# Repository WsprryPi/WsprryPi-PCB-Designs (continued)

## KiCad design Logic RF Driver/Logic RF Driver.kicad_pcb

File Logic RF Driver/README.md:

# Logic RF Driver

This two-layer board takes a raw 3.3 V CMOS clock and drives it through two paralleled SN74LVC2T45DCUR outputs powered from 5 V. Its target range is 137 kHz–145 MHz. Connect the output to a filter for the selected band, then to a 50-ohm load. The board has no RF power, thermal, emissions, or source-compatibility measurements.

Open [the KiCad project](Logic%20RF%20Driver.kicad_pro) for the schematic and PCB. The project includes the [symbols, footprints, and STEP models](libraries/README.md); their paths use `${KIPRJMOD}`.

## Connections

| Connector | Pin | Connection |
| --- | --- | --- |
| J1, CLOCK IN | Center | Raw 0–3.3 V CMOS clock from a Pico GPIO, Pi GPIO, or Si5351 CLK output |
| J1 | Shield | Ground |
| J2, POWER | 1 | +3.3 V for VCCA and DIR |
| J2 | 2 | +5 V for VCCB |
| J2 | 3 | Common ground |
| J3, RF TO LPF | Center | RF output through C4 to the selected-band filter and load |
| J3 | Shield | Ground |

Connect one clock source at a time, with a common ground for the source, supplies, board, filter, and load. J1 has no 50-ohm termination. The source must supply the desired frequency at valid logic levels; not every Pico, Pi, or Si5351 configuration can generate 145 MHz.

## Circuit

A1 and A2 share the clock input. B1 and B2 connect directly together, with no output resistors. DIR is tied to +3.3 V for A-to-B translation. R1 pulls the input low when it is undriven. C1 bypasses the 3.3 V supply, C2/C3 bypass the 5 V supply, and C4 blocks DC at the output.

The indicator samples `RF_RAW` on the U1 side of C4, through R2 (220 ohms) and C5 (10 nF). D1 is a BAT54S detector, Q1 is an MMBT3904, and D2 is the LED fed from +3.3 V through R4 (680 ohms). R3 is 1 Mohm, and C6 is 10 nF. C6 sits beside D1, with a 1.46 mm cathode connection and a nearby ground via. It stores rectified charge for Q1, while R3 provides a discharge path. The passive and LED footprints are 0603; D1 and Q1 use SOT-23. The detector loads U1's output stage. See the [input-loading study](INPUT-LOADING.md) for the R2 trade-off; its effect on RF output and total supply current is unmeasured and not included in the comparison model.

[TI's datasheet](https://www.ti.com/lit/ds/symlink/sn74lvc2t45.pdf) allows tying two outputs together for stronger drive. The device's electrical and thermal limits apply. Output current sharing and RF power across the target range are unmeasured on this board.

### Why the input is DC-coupled and C4 is on the output

The input needs a ground-referenced LOW and HIGH, so J1 is DC-coupled to A1/A2. R1 keeps it low if the clock source is disconnected or has high impedance. Putting a capacitor ahead of this pull-down removes the DC reference and can produce negative excursions or an unreliable HIGH. An AC-coupled clock or sine-wave source needs a separate bias and conditioning circuit.

The output capacitor has a different job: C4 removes the waveform's average voltage at the filter input. A 0–5 V waveform at 50% duty cycle has a nominal 2.5 V average, provided the downstream circuit gives it a DC return. The signal conductor is DC-blocked; the grounds are connected. See the [C4 impedance and bias analysis](C4-SELECTION.md).

## Parts and assembly

| References | Selected part | Specification | JLCPCB class |
| --- | --- | --- | --- |
| U1 | SN74LVC2T45DCUR / C15741 | VSSOP-8; dual-supply translator | Extended |
| R1 | 0603WAF1002T5E / C25804 | 10 kohms; 1%; 0.1 W; 0603 | Basic |
| R2 | 0603WAF2200T5E / C22962 | 220 ohms; 1%; 0.1 W; 0603 | Basic |
| R3 | 0603WAF1004T5E / C22935 | 1 Mohm; 1%; 0.1 W; 0603 | Basic |
| R4/R5 | 0603WAF6800T5E / C23228 | 680 ohms; 1%; 0.1 W; 0603 | Basic |
| C1/C2 | CC0603KRX7R9BB104 / C14663 | 100 nF; 10%; 50 V; X7R; 0603 | Basic |
| C3/C4 | CL10A105KB8NNNC / C15849 | 1 uF; 10%; 50 V; X5R; 0603 | Basic |
| C5/C6 | 0603B103K500NT / C57112 | 10 nF; 10%; 50 V; X7R; 0603 | Basic |
| D1 | BAT54S,215 / C47546 | 30 V; 200 mA; dual series Schottky; SOT-23 | Extended |
| D2/D3 | KT-0603R / C2286 | Red LED; 0603 | Basic |
| Q1 | MMBT3904(RANGE:100-300) / C20526 | NPN; 40 V; 200 mA; SOT-23 | Basic |

The sixteen-component [BOM](BOM.csv) covers U1, Q1, R1-R5, C1-C6, and D1-D3. Every assembly position has a selected ordering code in the hidden `LCSC Part #` field. The saved **JLCPCB** BOM preset exports the assembly columns and groups matching parts; see the [BOM export instructions](LCSC-PARTS.md#jlcpcb-bom-export). D2 indicates driver-output activity, and D3 indicates the 3.3 V supply through its own R5. J1/J2/J3 are visible in the schematic, board, and rendering, but excluded from the BOM and not marked DNP. J1/J3 use the Adafruit 1865 edge-launch SMA footprint. J2 has a shared footprint for an Adafruit 2136 three-position screw terminal or a straight 1×3 pin header, with 2.54 mm pitch, 1.2 mm holes, and 2.0 mm pads. The screw terminal is the default assembly option. Its body overhangs the board edge by 1.25 mm. The footprint silkscreen ends inside the board edge, while the fab outline and courtyard show the full housing. C1–C3 lie outside its courtyard. See [ordering codes and supplier information](LCSC-PARTS.md) and the [connector and assembly notes](CONNECTORS.md).

## Layout and checks

The board is 27.08 × 16.00 mm, with 1 mm corner radii and a nominal thickness of 1.57 mm. It has two copper layers, 83 front-layer track segments and 41 ground vias. Both layers have a filled ground zone, and stitching runs along both sides of the short RF paths. The placement grid is 0.25 mm, though several component anchors sit off it. See [layout details](PCB-LAYOUT.md).

The configured CAD checks report zero ERC violations, zero unconnected items, and zero schematic-parity issues. The saved PCB has filled ground zones and reports zero DRC violations, zero unconnected items, and zero schematic-parity issues. A local edge-contact rule covers the J1/J3 SMA lands, and all other copper retains the 0.50 mm edge setback. All connections are routed. Connector fit and RF performance remain unmeasured. All PCB DRC and schematic ERC categories are enabled. [Validation](VALIDATION.md) describes the warning checks.

## Project text variables

The PCB Editor exposes these settings under **File → Board Setup → Text & Graphics → Text Variables**. Schematic Setup also includes these definitions. The project file holds 16 variables for title blocks, headings, supply notes, and board labels; they are not machine-wide environment variables.

Edit the project file externally with the KiCad editors and the project closed. KiCad keeps settings in memory and can overwrite an external edit when it closes. Reopen the project to load the file, and check label fit and DRC for the resulting labels. See the [KiCad text-variable reference](https://docs.kicad.org/10.0/en/pcbnew/pcbnew.html#text_variables).

## Research and limitations

The [30 m transmitter/filter study](30M-TRANSMITTER.md) connects the board’s behavioral circuit model directly to the five-element L-first filter and the original seven-element C-first filter at 10.1401 MHz. The nominal L-first case predicts 65.5 mW into 50 ohms and a third harmonic near −76 dBc. Coil Q and line-length sensitivities and finer-timestep checks are included. The C-first comparison demands substantially higher modeled output current. Neither case establishes physical performance, safe current, or emissions compliance.

The [single-chip THS3491 amplifier study](THS3491-STUDY.md) evaluates a separate gain-of-five PA driven by this board, with input and output low-pass filters, supply current, and thermal estimates. Its nominal half-voltage divider predicts about 231–247 mW at the filtered load; the higher-drive divider predicts about 331–356 mW. It does not establish 500 mW across the full range. The PA is absent from the schematic, PCB, and BOM.

The [dual-chip THS3491 study](THS3491-DUAL-STUDY.md) evaluates TI's parallel RGT load-sharing core with inductor-first filters. It predicts about 335–357 mW at the filtered load with the 0.6 divider, compared with 330–344 mW from the matched single-RGT control. Each chip dissipates about 0.92 W, while total IC heat is about 1.84 W. Higher modeled output at 145 MHz requires a pin swing above TI's recommended linear envelope; the study does not establish 500 mW across the full range.

The [25-to-50-ohm THS3491 matching-filter study](THS3491-MATCHING-STUDY.md) evaluates a single RGT amplifier with an inductor-first matching/output filter. It predicts approximately 500 mW at nominal drive and about 600 mW with adjustment headroom. Filter tolerances and losses limit fixed-drive output, and approximately 2 W of IC heat requires a suitable PA thermal layout. It establishes nominal electrical feasibility, with continuous-duty reliability unqualified.

The [dual-chip THS3491 matching-filter study](THS3491-DUAL-MATCHING-STUDY.md) compares two RGT amplifiers with the same 25-to-50-ohm filters, source, losses, and tolerance cases. The 0.50 divider predicts 536–547 mW, with up to 1.32 W of heat per chip and 2.64 W total. The 0.55 divider gives nominal adjustment headroom at 645–662 mW and keeps the selected ±5% output-filter tolerance cases above 500 mW. Combined poorer-Q, higher-loss, and tolerance cases fall below 500 mW, and actual cooling and RF performance remain unqualified. The PA is absent from this project's CAD and BOM.

The [output-sharing resistor study](OUTPUT-SHARING.md) evaluates independent resistors on B1/B2. TI permits directly paralleling the two outputs, which is the design baseline. For optional resistive isolation, 10 ohms per output gives about 65–68 mW into 50 ohms in the model. Hypothetical skew tests do not demonstrate a need for these resistors. These resistors are absent from the schematic, PCB, and BOM.

The [board circuit simulation](BOARD-SIMULATION.md) includes the RF_RAW detector and both LED branches. Its nominal model predicts about 82.5 mW at 137 kHz and 79.9 mW at 145 MHz into 50 ohms, excluding filter and connector loss. Assumed-skew stress cases explore model sensitivity; their current peaks are not validated predictions of this IC or evidence of a timing fault. The study has no extracted PCB or supply-network model and does not establish thermal or full-band reliability.

The [SN74LVC2T45 versus BS170 comparison](COMPARISON.md) predicts about 84.32 mW at 137 kHz and 83.03 mW at 145 MHz for the paralleled logic stage, excluding filter loss. It uses a behavioral logic model, ideal supplies, and a bias-dependent C4 fit. These figures are simulated, not measured, and exclude the detector branch. The separate [detector study](INPUT-LOADING.md) gives about 82.48 mW at 137 kHz and 79.89 mW at 145 MHz with R2 at 220 ohms, using surrogate semiconductor and LED models. The ideal-choke BS170 results are diagnostic only because they fail numerical robustness checks. See [model scope](MODEL-SCOPE.md).

Project-owned work follows the repository [MIT license](../LICENSE.md). Library assets retain the [KiCad library license and exception](libraries/KICAD-LIBRARY-LICENSE.md). Manufacturer data retain their own terms.

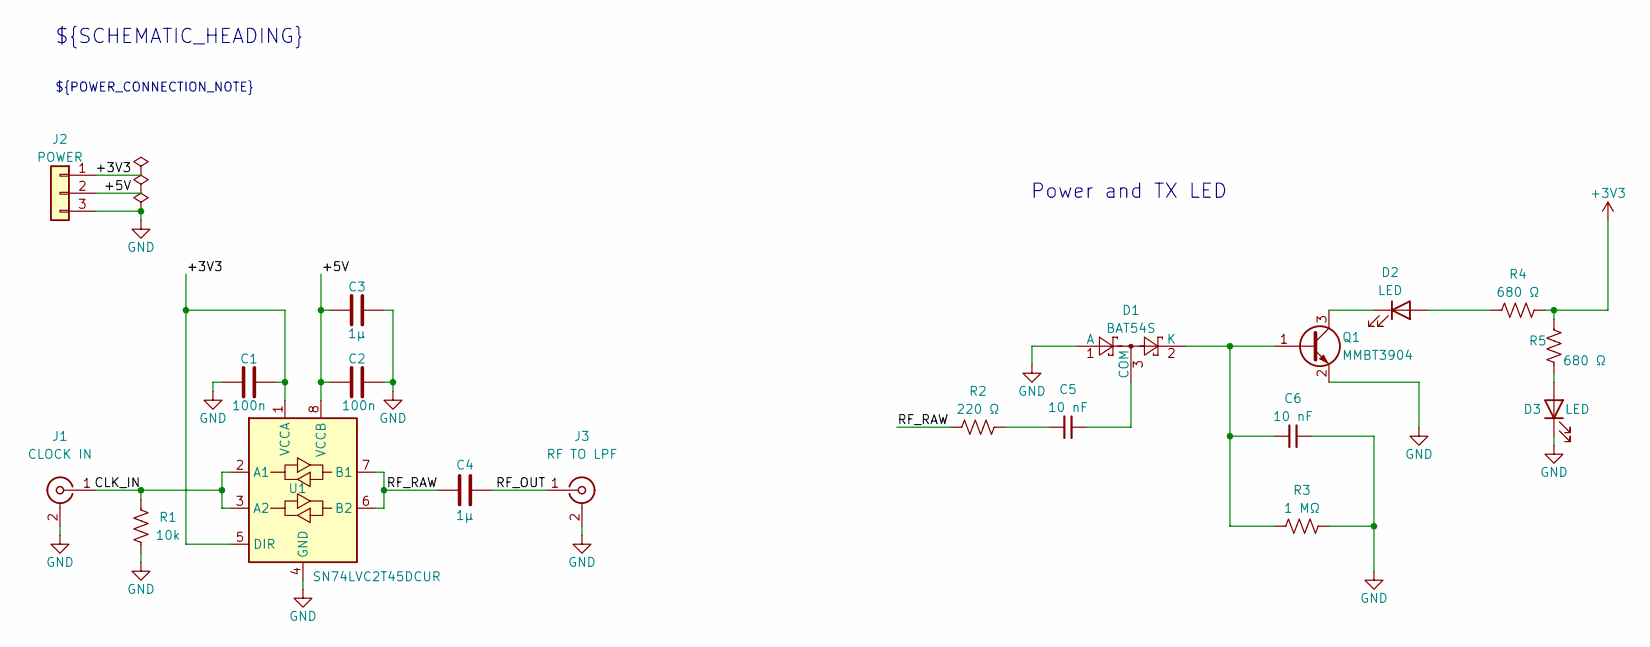
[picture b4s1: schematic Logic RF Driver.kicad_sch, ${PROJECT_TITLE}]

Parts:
C1, C2: 100n; C_0603_1608Metric; Voltage 50 V; Tolerance ±10%; MPN CC0603KRX7R9BB104; LCSC Part # C14663
C3, C4: 1μ; C_0603_1608Metric; Voltage 50 V; Tolerance ±10%; MPN CL10A105KB8NNNC; LCSC Part # C15849
C5, C6: 10 nF; C_0603_1608Metric; Voltage 50 V; Tolerance 10%; MPN 0603B103K500NT; JLCPCB Class Basic
D1: BAT54S; SOT-23; MPN BAT54S,215; JLCPCB Class Extended
D2, D3: LED; LED_KT0603R; MPN KT-0603R; JLCPCB Class Basic
J1: CLOCK IN; SMA_Adafruit_1865_EdgeLaunch; MPN 1865
J2: POWER; Power_1x03_P2.54mm_Header_or_Adafruit_2136; MPN 2136
J3: RF TO LPF; SMA_Adafruit_1865_EdgeLaunch; MPN 1865
Q1: MMBT3904; SOT-23; MPN MMBT3904(RANGE:100-300); JLCPCB Class Basic
R1: 10k; R_0603_1608Metric; Tolerance 1%; Rating 0.1 W; MPN 0603WAF1002T5E; LCSC Part # C25804
R2: 220 Ω; R_0603_1608Metric; Voltage 75 V; Rating 0.1 W; MPN 0603WAF2200T5E; JLCPCB Class Basic
R3: 1 MΩ; R_0603_1608Metric; Voltage 75 V; Rating 0.1 W; MPN 0603WAF1004T5E; JLCPCB Class Basic
R4, R5: 680 Ω; R_0603_1608Metric; Voltage 75 V; Rating 0.1 W; MPN 0603WAF6800T5E; JLCPCB Class Basic
U1: SN74LVC2T45DCUR; VSSOP-8_2.3x2mm_P0.5mm; MPN SN74LVC2T45DCUR; LCSC Part # C15741

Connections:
+3V3: C1.1, J2.1, R4.2, R5.2, U1.1 (VCCA), U1.5 (DIR)
/+5V: C2.1, C3.1, J2.2, U1.8 (VCCB)
/CLK_IN: J1.1 (In), R1.1, U1.2 (A1), U1.3 (A2)
/RF_OUT: C4.2, J3.1 (In)
/RF_RAW: C4.1, R2.1, U1.6 (B2), U1.7 (B1)
GND: C1.2, C2.2, C3.2, C6.2, D1.1 (A), D3.2 (K_1), J1.2 (Ext), J2.3, J3.2 (Ext), Q1.2 (E), R1.2, R3.2, U1.4 (GND)
unnamed: C5.1, R2.2
unnamed: C5.2, D1.3 (COM)
unnamed: C6.1, D1.2 (K), Q1.1 (B), R3.1
unnamed: D2.1 (A_2), R4.1
unnamed: D2.2 (K_1), Q1.3 (C)
unnamed: D3.1 (A_2), R5.1

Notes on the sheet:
${SCHEMATIC_HEADING}
Power and TX LED
${POWER_CONNECTION_NOTE}

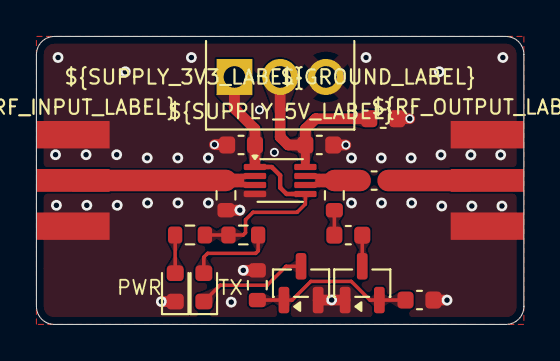
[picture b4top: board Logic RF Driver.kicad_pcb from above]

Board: 2 copper layers, 27.1 x 16.0 mm, 19 parts (0 on the bottom side), 12 nets.

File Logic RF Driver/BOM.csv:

"Comment","Designator","Footprint","LCSC Part #","Quantity","Manufacturer","MPN"
"100n","C1,C2","SN74LVC2T45_Amp:C_0603_1608Metric","C14663","2","YAGEO","CC0603KRX7R9BB104"
"1μ","C3,C4","SN74LVC2T45_Amp:C_0603_1608Metric","C15849","2","Samsung Electro-Mechanics","CL10A105KB8NNNC"
"10 nF","C5,C6","SN74LVC2T45_Amp:C_0603_1608Metric","C57112","2","FH (Guangdong Fenghua Advanced Tech)","0603B103K500NT"
"BAT54S","D1","SN74LVC2T45_Amp:SOT-23","C47546","1","Nexperia","BAT54S,215"
"LED","D2,D3","SN74LVC2T45_Amp:LED_KT0603R","C2286","2","Hubei KENTO Elec","KT-0603R"
"MMBT3904","Q1","SN74LVC2T45_Amp:SOT-23","C20526","1","Jiangsu Changjing Electronics Technology Co., Ltd.","MMBT3904(RANGE:100-300)"
"10k","R1","SN74LVC2T45_Amp:R_0603_1608Metric","C25804","1","UNI-ROYAL(Uniroyal Elec)","0603WAF1002T5E"
"220 Ω","R2","SN74LVC2T45_Amp:R_0603_1608Metric","C22962","1","UNI-ROYAL(Uniroyal Elec)","0603WAF2200T5E"
"1 MΩ","R3","SN74LVC2T45_Amp:R_0603_1608Metric","C22935","1","UNI-ROYAL(Uniroyal Elec)","0603WAF1004T5E"
"680 Ω","R4,R5","SN74LVC2T45_Amp:R_0603_1608Metric","C23228","2","UNI-ROYAL(Uniroyal Elec)","0603WAF6800T5E"
"SN74LVC2T45DCUR","U1","SN74LVC2T45_Amp:VSSOP-8_2.3x2mm_P0.5mm","C15741","1","Texas Instruments","SN74LVC2T45DCUR"

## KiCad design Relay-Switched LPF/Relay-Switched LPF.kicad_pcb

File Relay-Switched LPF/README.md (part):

# Relay-Switched LPF

Independent KiCad reconstruction of the **QRP Labs Ultimate relay-switched LPF carrier, PCB Rev. 5**. Open [Relay-Switched LPF.kicad_pro](Relay-Switched%20LPF.kicad_pro). The editable [schematic](Relay-Switched%20LPF.kicad_sch), [PCB](Relay-Switched%20LPF.kicad_pcb), and [schematic PDF](Relay-Switched%20LPF.pdf) belong to this project.

**Engineering reconstruction, drawing revision v0.0.1; not qualified for fabrication or use.** The published circuit is reconstructed, and a new two-layer layout is provided inside an 80 × 37 mm outline. This is not an original QRP Labs CAD release, an exact trace copy, or a verified mechanical replacement. Read [VALIDATION.md](VALIDATION.md) for actual checks and remaining findings before ordering anything.

## What is included

- Five Panasonic TX2-5V DPDT relay channels, five 1N4148 flyback diodes, and ten four-position LPF sockets.
- An underside 2 × 5 host socket, active-low band controls, separate coil-supply link, five output selectors, a final-filter input selector, and an optional output-ground bypass.
- Five individual antenna solder-terminal pairs, a final-output terminal pair, and alternative generic vertical and edge SMA pad groups.
- Independent [symbol library](relay-switched-lpf.kicad_sym), [footprint library](relay-switched-lpf.pretty/), and `${KIPRJMOD}` library tables. No references to other repository projects or machine-specific library locations.
- [Project-local 3D models](relay-switched-lpf.3dshapes/README.md) for the carrier components, optional SMA connectors, and default fitted wire links; the four mounting-hole footprints are also local.
- [Reconstruction generator](design/generate.py), [routing script](design/route.py), and [connectivity audit](design/audit.py). These are reproducibility tools; the saved native CAD files remain authoritative after hand edits.
- Ten four-pin LPF connectors use the standard KiCad boxed `Conn_01x04` appearance, adapted in the project-local `LPF_IN`/`LPF_OUT` symbols; see [attribution and license](KICAD-LIBRARY-LICENSE.md#four-pin-connector-symbols).
- J21–J26 use the matching two-pin boxed connector appearance, adapted locally from KiCad `Conn_01x02`; see [attribution](KICAD-LIBRARY-LICENSE.md#two-pin-antenna-connector-symbol).
- W1–W9 use matching boxed two-/three-pin connector symbols. These are drawing conventions; the PCB retains bare wire-link pads and the assembly options below.
- J1 uses the same boxed connector style for its ten schematic pins; its physical footprint remains the underside 2 × 5 host socket.
- X1/X2 use project-local copies of the KiCad `Conn_Coaxial` symbol, with center contact 1 on `LPF1_OUT` and shield 2 on `GND_OUT`; their vertical/edge SMA footprints remain distinct.
- Ground markings use the project-local `GND` power symbol matching W8’s triangular ground. Main ground is global `GND`; `GND_OUT` remains separate. A local `PWR_FLAG` records the host-supplied ground for ERC.
- A visibly wired schematic arranged like the published diagram: relay coils and flyback diodes above the shared RF input bus, five filter columns, and a shared output bus below. Relay units A/B/C are the coil/input pole/output pole of the same physical relay. [Redraw tool](design/redraw_schematic.py) updates the schematic and its local symbol graphics without writing the PCB.

The plug-in filter circuits, band-dependent inductors/capacitors, Ultimate3S transmitter, sixth relay/filter on that transmitter, GPIO drivers, enclosure, and spacers are external. No arbitrary filter bands or component values have been selected.

## Default circuit and assembly

Install the highest-frequency LPF in **slot 1**, on the right. Energizing one of relays 2–5 selects its filter, whose output feeds slot 1 through the common `RFO` bus. Energizing relay 1 feeds its filter directly from `RFI`. With no carrier relay energized, an external filter-0 signal on `RFO` can still pass through slot 1. Filters 2–5 have both RF terminals grounded when their relays are at rest.

The saved PCB represents **unbridged wire-link pads**. Fit these six separate wire links for the default LPF configuration:

| Link | Fit | Function |
| --- | --- | --- |
| W1 | 1–2 | Connect `+5V` to `RELAY_VPLUS` |
| W2 | **Open** | Slot-1 relay output selector; final output already comes directly from LPF1 |
| W3, W4, W5, W6 | Each 1–2 | Connect relays 2–5 to `RFO` |
| W7 | 1–2 | Feed relay-1 normally closed input from `RFO` |
| W8 | **Open** | Preserve isolated final output return |
| W9 | **Open** | Optional LPF1-output to relay-1 second-pole COM link |

W2–W6 each use pin 1 for the relay's output NO contact, pin 2 for `RFO`, and pin 3 for the corresponding individual `ANTn` terminal. W7 pins 1/2/3 are `RFO` / `FINAL_NC` / `GND`. W8 pins 1/2 are `GND` / `GND_OUT`. W9 pins 1/2 are `LPF1_OUT` / `FINAL_RELAY_COM`; it represents the separately accessible RF pads by relay 1 in the source circuit. The second pole of relay 1 is not in the default RF path. Link designators and pad ordering are assigned by this reconstruction, not original QRP Labs designators. An unfitted selector pad still has a routed net; it is intentionally not shorted by copper.

`GND_OUT` joins X1/X2 returns, J26 pin 2, and slot-1 output-socket pins 3/4. It remains separate from main `GND`; slot-1 output-socket pins 1/2 carry RF. Do not bridge these returns through mounting hardware, coax shields, or test equipment without considering the intended filter return path. W8 represents the original optional ground-bridge pad pairs as one two-terminal link, not a default connection.

The circuit retains alternate output selection pads, but this revision has only been audited against the default LPF configuration. Alternate BPF or separate-antenna assembly requires a separate connection review. The SMA groups are permanently connected to `LPF1_OUT`, not `RFO`; those nets are distinct.

For a **separate regulated 5 V relay supply**, leave W1 **open**, connect supply positive to **W1 pin 2 (`RELAY_VPLUS`)**, and connect supply negative to main **`GND`**, shared with the host/low-side drivers. Do not use `GND_OUT` as the coil return. W1 pin 1 remains on host `+5V`; keep W1 open so the two positive supplies are not paralleled. The relays remain 5 V types. Use external sink drivers compatible with the coil supply and host power sequencing. The default shared-supply configuration still fits W1 pins 1–2.

This cathode-to-coil-supply connection is an intentional adaptation of the reconstructed QRP Labs circuit. CAD connectivity and rule checks pass; separate-supply switching behavior has not been bench-qualified.

## Host and module pin maps

J1 is on **B.Cu**, opposite the relays. In a component-side/top view, with slot 5 on the left and slot 1 on the right, J1's odd-numbered column is on the left, and its even-numbered column is on the right. Read each row from the input-socket edge toward the output-socket edge:

| Left pin | Net | Right pin | Net |
| --- | --- | --- | --- |
| 1 | +5V | 2 | BAND5_N |
| 3 | BAND3_N | 4 | BAND4_N |
| 5 | BAND1_N | 6 | BAND2_N |
| 7 | GND | 8 | RFI |
| 9 | GND | 10 | RFO |

This numeric convention is assigned to the published labeled pad arrangement. Confirm the mating host's numbering and orientation; do not infer compatibility from a generic 2 × 5 socket name. In top view, J1 pin 1 is at board coordinate (2.54, 8.26) mm, with 2.54 mm row/column pitch.

Band controls sink the relay-coil current. The nominal 5 V, 140 mW coil corresponds to approximately 28 mA. Use a suitable external sink driver for Raspberry Pi/Pico GPIO; the carrier contains no transistor or level shifter. Energize **at most one** band input at a time and mute RF during switching. D1–D5 cathodes connect directly to `RELAY_VPLUS`, the same rail as the relay coil positives, so flyback current stays on the coil-supply rail.

| Item | Pin assignments |
| --- | --- |
| RLn | 1 coil+, 12 coil−; 8 NO/input bus, 9 COM/filter input, 10 NC; 5 NO/output selector, 4 COM/filter output for slots 2–5 (separate FINAL_RELAY_COM for slot 1), 3 NC/main ground |
| Dn | 1 cathode/+5V; 2 anode/BANDn_N |
| J2/J4/J6/J8/J10 | LPF1/2/3/4/5 input: pins 1/2 GND; pins 3/4 signal |
| J3/J5/J7/J9/J11 | LPF1/2/3/4/5 output: pins 1/2 signal; pins 3/4 GND except LPF1 pins 3/4 use GND_OUT |
| J21–J25 | ANT1–ANT5: pin 1 RF, pin 2 main GND |
| J26, X1, X2 | Pin 1 final RF output, pin 2 isolated GND_OUT; repeated X1/X2 pin 2 pads are intentional |

Input sockets run pin 1 left to pin 4 right in top view. Output sockets run pin 4 left to pin 1 right. Match module IN/OUT markings. There is no guaranteed RF power, frequency range, insertion loss, or isolation rating for the reconstructed layout.

## Geometry, population, and model limits

| Feature | Implemented geometry | Evidence / limit |
| --- | --- | --- |
| Outline | 80 × 37 mm, two layers, four tangent R3 mm corner fillets | Overall published size retained; radius selected for this reconstruction, not a measured original-board radius |
| Filter sockets | 2.54 mm pitch; 33.02 mm input/output row spacing; 13.97 mm slot spacing | Pitch-based reconstruction of the placement/trace drawings; confirm on real modules |
| Mounts | Four 3.2 mm NPTH holes at (3,3), (77,3), (3,34), (77,34) mm | **Inferred**, not dimensioned in the manual; must be measured against host/spacers |
| Relays | 15 × 7.4 mm body; 5.08 mm pin-row separation, 5.08/2.54/2.54 mm longitudinal pin spacing; 1 mm drills | Standard TX2 terminal pattern reconstructed from available pin/dimension evidence; verify actual supplied surplus relay |
| Diodes | DO-35 axial, 7.62 mm lead pitch | New footprint choice, not a measured original lead bend |
| Wire links / terminals | Bare 1.8 mm pads, 1 mm holes, 2.54 mm pitch | Layout adaptation; not plastic headers |
| X1 | Generic vertical SMA, central signal and four returns at ±2.54 mm; center (75.819, 23) mm | CAD edge and courtyard checks pass; no selected manufacturer/order code or verified physical fit |
| X2 | Generic double-sided edge SMA land pattern; footprint origin (78.5, 12) mm, with RF and isolated-return layer transitions | CAD clearance/connectivity checks pass; no selected connector or qualified board thickness |
| Routing | New 0.30 mm two-layer traces with ground and isolated-return fills | Not an exact original trace geometry or controlled-impedance stackup |

The terminal and link locations have been adjusted within the published outline to make the reconstruction routable. Consequently, mating compatibility is not established by matching the board's outer dimensions. X1 is an alternative to X2/J26; using a short coax pigtail on the output pads avoids assuming a generic SMA fits underneath a filter. Review vertical clearances to the plug-in filters and the original warning about vertical SMA interference.

The output-area DRC repair moves RL1 left 0.762 mm and X1 left 0.381 mm from their initial placements, preserving socket/mounting coordinates. Nearby RFI, LPF1 input, and relay-1 COM traces are rerouted. Two 0.65/0.30 mm vias join X2's RF lands and its isolated output return between copper layers. The latest hand edit extends both main-ground pours across the board, with clearance around the separate output-return pads and traces. Two dedicated return vias and short traces now connect X2’s front/back ground lands. KiCad 10.0.6 reports zero rule violations, unconnected items, or schematic-parity findings; see [current validation](VALIDATION.md#output-return-layer-repair--2026-11-13). Physical connector fit and RF qualification remain open.

The 3D viewer now uses seven local STEP/VRML assets across 29 model instances: the 21 normal carrier components, both optional SMA alternatives, and six fitted wire links. The socket and diode STEP files are unmodified KiCad assets; the relay, SMA, and wire models are documented original nominal previews. No unrelated relay/connector model is silently substituted. Bare terminals, open links, and mounting holes have no invented part bodies. See [model coverage and limits](relay-switched-lpf.3dshapes/README.md) and [KiCad asset terms](KICAD-LIBRARY-LICENSE.md).

Twenty-one normal carrier components are needed before wire links: five relays, five diodes, ten four-way sockets, and one ten-way underside socket. SMA hardware is optional; filter modules, six default wire links, and mounting hardware are separate assembly items. The two SMA previews are alternatives, not an instruction to assemble both. See [BOM.csv](BOM.csv).

All 42 saved board footprints, including the four mounting holes, resolve to eleven project-local footprint definitions. The six fitted wire links use model-bearing variants whose pad geometry is identical to the bare versions. Every schematic symbol is in the independent local symbol library. Keep the entire project folder, including `.pretty` and `.3dshapes`, together when copying it.

## Letter sheets and shared title-block fields

The schematic fits on one **US Letter landscape sheet, 11 × 8.5 inches**, matching the selected ANSI A page setting in both editors. The compact symbols use a standard 25 mil schematic connection grid. The PCB drawing-sheet size is the same; its actual board geometry is unchanged by this page-format work.

Edit shared values under **Schematic Setup or Board Setup → Project → Text Variables**. Both title blocks refer to the same project variables, so set these values once rather than replacing their `${DOC_...}` references in Page Settings:

| Project variable | Shared field | Current value |
| --- | --- | --- |
| `DOC_TITLE` | Title | Relay-Switched LPF |
| `DOC_DATE` | Date | 11/13/2026 |
| `DOC_REVISION` | Revision | v0.0.1 |
| `DOC_COMPANY` | Company / author | Lee Bussy [AA0NT] |
| `DOC_COMMENT1`–`DOC_COMMENT4` | Comments 1–4 | Empty |
| `DOC_COMMENT5`–`DOC_COMMENT9` | Additional optional comment placeholders | Define shared variables if used |

These are native [KiCad project text variables](https://docs.kicad.org/10.0/en/eeschema/eeschema.html), stored in the `.kicad_pro` file and usable by both editors. The date is an explicit shared value, not an automatic clock. [Shared-field setup tool](design/shared_fields.py) installs the references while retaining existing project values; the redraw and full-generation tools preserve those values on later runs. The filenames and sheet numbers remain editor-specific.

## Rebuilding and checking

Creation and checks use **KiCad 10.0.6**. The generators overwrite this project's CAD; save hand edits before regenerating. Run `design/generate.py` and then `design/route.py` using a Python installation with KiCad's `pcbnew`, wxPython, and NumPy. On macOS, the bundled KiCad Python requires access to the logged-in display session. Routing refuses an already routed board.

The full generator invokes `design/redraw_schematic.py` after creating the initial circuit. To rebuild only the schematic presentation from the saved references and connection map, run `python3 design/redraw_schematic.py`; this uses only Python's standard library. Re-export the PDF and rerun ERC and the connectivity audit afterward. Net labels are retained for names, host connections, and ground references; the filter and relay interconnections are drawn as wires.

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
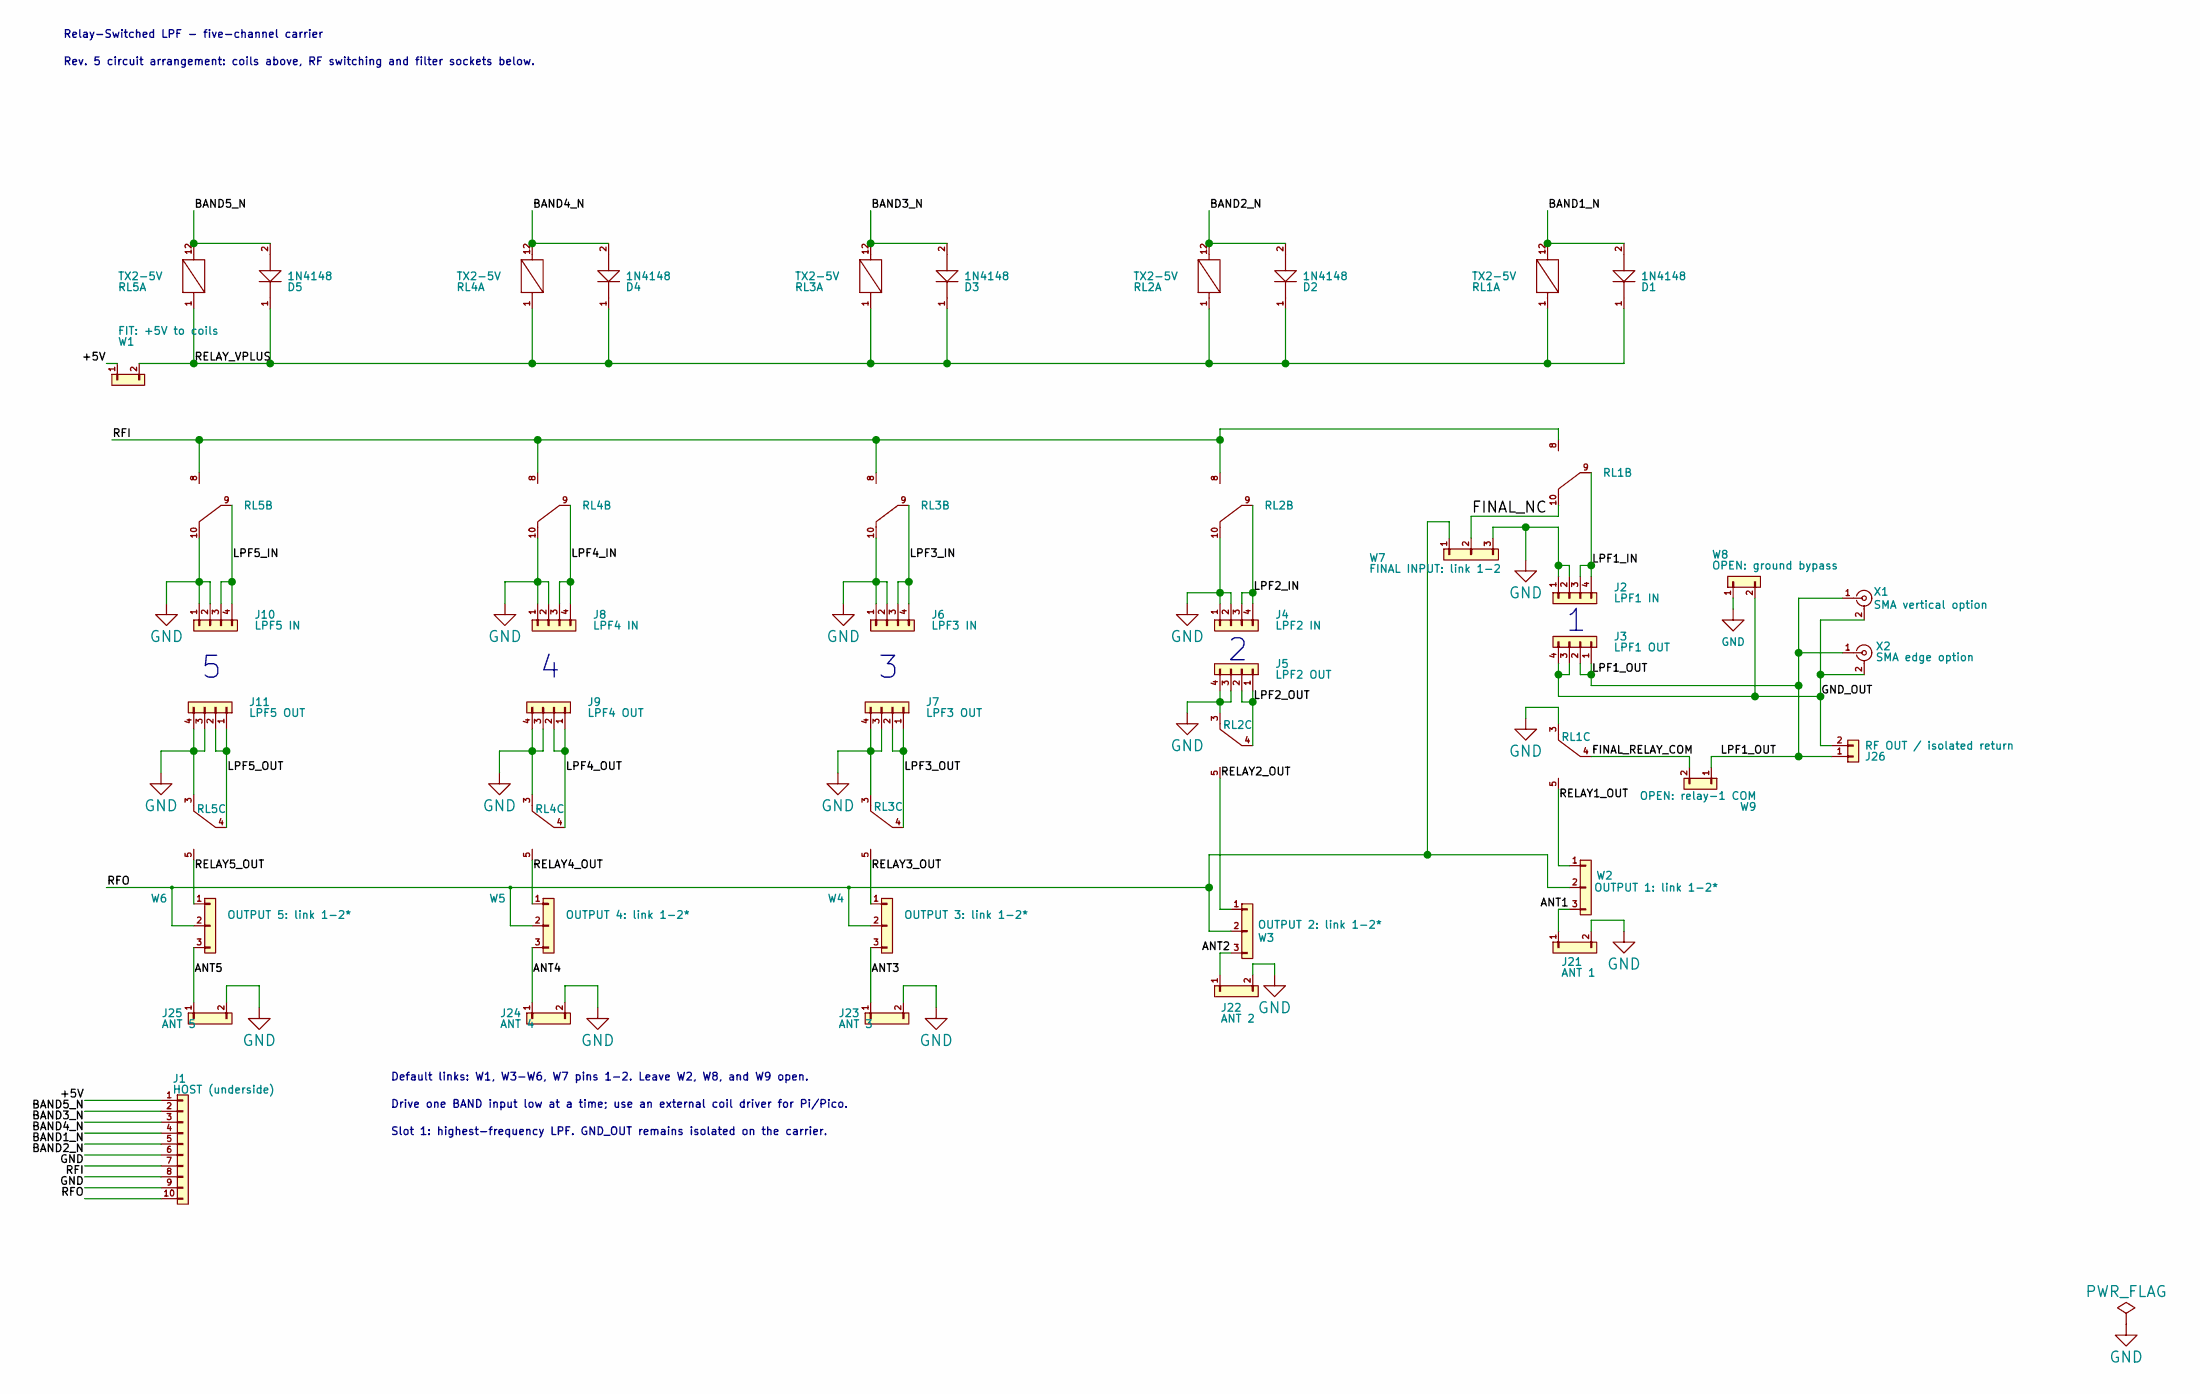
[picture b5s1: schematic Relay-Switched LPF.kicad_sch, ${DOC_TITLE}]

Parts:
D1, D2, D3, D4, D5: 1N4148; D_DO35_P7.62
J1: HOST (underside); Host_2x05
J2: LPF1 IN; Socket_1x4
J3: LPF1 OUT; Socket_1x4
J4: LPF2 IN; Socket_1x4
J5: LPF2 OUT; Socket_1x4
J6: LPF3 IN; Socket_1x4
J7: LPF3 OUT; Socket_1x4
J8: LPF4 IN; Socket_1x4
J9: LPF4 OUT; Socket_1x4
J10: LPF5 IN; Socket_1x4
J11: LPF5 OUT; Socket_1x4
J21: ANT 1; Wire_1x2
J22: ANT 2; Wire_1x2
J23: ANT 3; Wire_1x2
J24: ANT 4; Wire_1x2
J25: ANT 5; Wire_1x2
J26: RF OUT / isolated return; Wire_1x2
RL1, RL2, RL3, RL4, RL5: TX2-5V; TX2_5V
W1: FIT: +5V to coils; Wire_1x2_Link12
W2: OUTPUT 1: link 1-2*; Wire_1x3
W3: OUTPUT 2: link 1-2*; Wire_1x3_Link12
W4: OUTPUT 3: link 1-2*; Wire_1x3_Link12
W5: OUTPUT 4: link 1-2*; Wire_1x3_Link12
W6: OUTPUT 5: link 1-2*; Wire_1x3_Link12
W7: FINAL INPUT: link 1-2; Wire_1x3_Link12
W8: OPEN: ground bypass; Wire_1x2
W9: OPEN: relay-1 COM; Wire_1x2
X1: SMA vertical option; SMA_Vertical_Generic
X2: SMA edge option; SMA_Edge_Generic

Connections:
/+5V: J1.1, W1.1
/ANT1: J21.1, W2.3
/ANT2: J22.1, W3.3
/ANT3: J23.1, W4.3
/ANT4: J24.1, W5.3
/ANT5: J25.1, W6.3
/BAND1_N: D1.2, J1.5, RL1.12
/BAND2_N: D2.2, J1.6, RL2.12
/BAND3_N: D3.2, J1.3, RL3.12
/BAND4_N: D4.2, J1.4, RL4.12
/BAND5_N: D5.2, J1.2, RL5.12
/FINAL_NC: RL1.10, W7.2
/FINAL_RELAY_COM: RL1.4, W9.2
/GND_OUT: J3.3, J3.4, J26.2, W8.2, X1.2 (Ext), X2.2 (Ext)
/LPF1_IN: J2.3, J2.4, RL1.9
/LPF1_OUT: J3.1, J3.2, J26.1, W9.1, X1.1 (In), X2.1 (In)
/LPF2_IN: J4.3, J4.4, RL2.9
/LPF2_OUT: J5.1, J5.2, RL2.4
/LPF3_IN: J6.3, J6.4, RL3.9
/LPF3_OUT: J7.1, J7.2, RL3.4
/LPF4_IN: J8.3, J8.4, RL4.9
/LPF4_OUT: J9.1, J9.2, RL4.4
/LPF5_IN: J10.3, J10.4, RL5.9
/LPF5_OUT: J11.1, J11.2, RL5.4
/RELAY1_OUT: RL1.5, W2.1
/RELAY2_OUT: RL2.5, W3.1
/RELAY3_OUT: RL3.5, W4.1
/RELAY4_OUT: RL4.5, W5.1
/RELAY5_OUT: RL5.5, W6.1
/RELAY_VPLUS: D1.1, D2.1, D3.1, D4.1, D5.1, RL1.1, RL2.1, RL3.1, RL4.1, RL5.1, W1.2
/RFI: J1.8, RL1.8, RL2.8, RL3.8, RL4.8, RL5.8
/RFO: J1.10, W2.2, W3.2, W4.2, W5.2, W6.2, W7.1
GND: J1.7, J1.9, J2.1, J2.2, J4.1, J4.2, J5.3, J5.4, J6.1, J6.2, J7.3, J7.4, J8.1, J8.2, J9.3, J9.4, J10.1, J10.2, J11.3, J11.4, J21.2, J22.2, J23.2, J24.2, J25.2, RL1.3, RL2.3, RL2.10, RL3.3, RL3.10, RL4.3, RL4.10, RL5.3, RL5.10, W7.3, W8.1

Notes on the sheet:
Slot 1: highest-frequency LPF. GND_OUT remains isolated on the carrier.
Relay-Switched LPF - five-channel carrier
Drive one BAND input low at a time; use an external coil driver for Pi/Pico.
Default links: W1, W3-W6, W7 pins 1-2. Leave W2, W8, and W9 open.
Rev. 5 circuit arrangement: coils above, RF switching and filter sockets below.

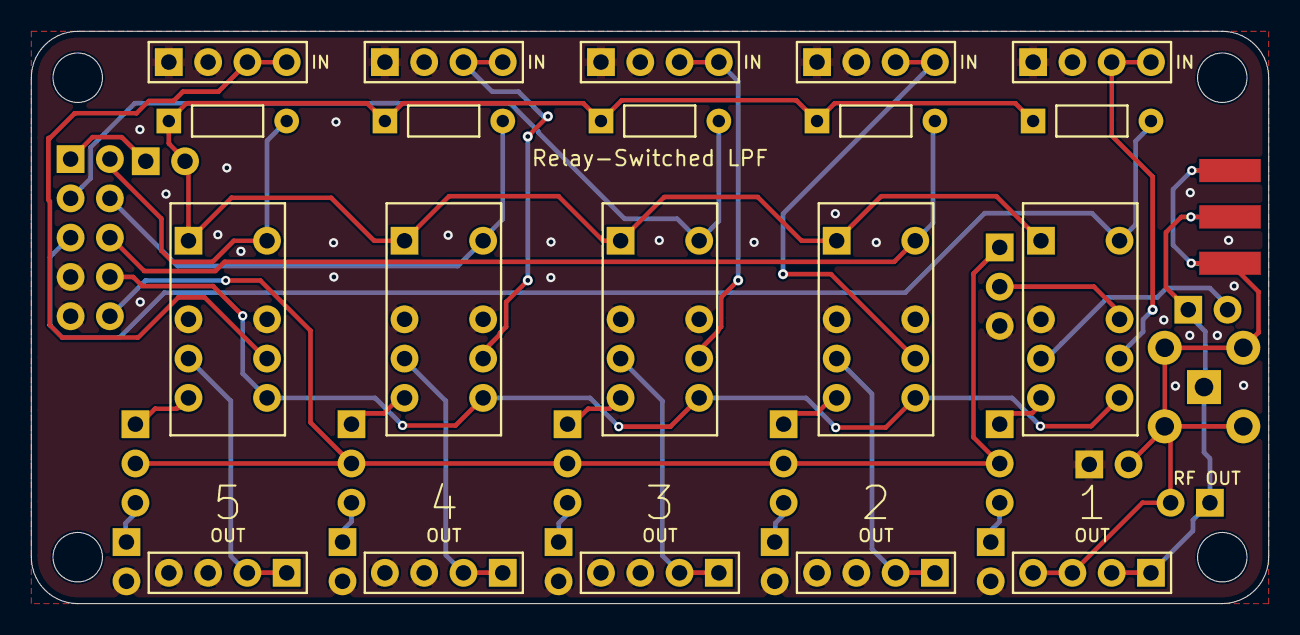
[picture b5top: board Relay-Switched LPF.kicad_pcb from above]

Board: 2 copper layers, 80.0 x 37.0 mm, 42 parts (1 on the bottom side), 33 nets.

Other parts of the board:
H1, H2, H3, H4: Mount 3.2 mm (inferred); MountingHole_3.2mm

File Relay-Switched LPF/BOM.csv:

References,Quantity,Description,Part or specification,Population
RL1-RL5,5,DPDT non-latching relay,Panasonic TX2-5V 5V coil,Required
D1-D5,5,Axial flyback diode,1N4148 DO-35,Required
J2-J11,10,LPF module female socket,1x04 2.54mm pitch through-hole,Required
J1,1,Underside host female socket,2x05 2.54mm pitch through-hole verify mating height,Required
W1 W3 W4 W5 W6 W7,6,Hand-fit wire link,Connect pins 1-2 per README,Default LPF configuration
W2 W8 W9,0,Unfitted optional link,Leave open in default assembly,Open
J21-J26,0,Bare RF wire terminals,PCB pads no purchased header required,Use as needed
X1,0,Optional vertical SMA,Generic pattern no selected order code,Optional fit unverified
X2,0,Optional edge SMA,Generic pattern no selected order code,Optional fit unverified
H1-H4,4,Mounting hardware,Builder choice measure hole positions and stack height,Mechanical fit unverified
External LPFs,5,Plug-in filter modules,Select band set separately highest frequency in slot 1,External

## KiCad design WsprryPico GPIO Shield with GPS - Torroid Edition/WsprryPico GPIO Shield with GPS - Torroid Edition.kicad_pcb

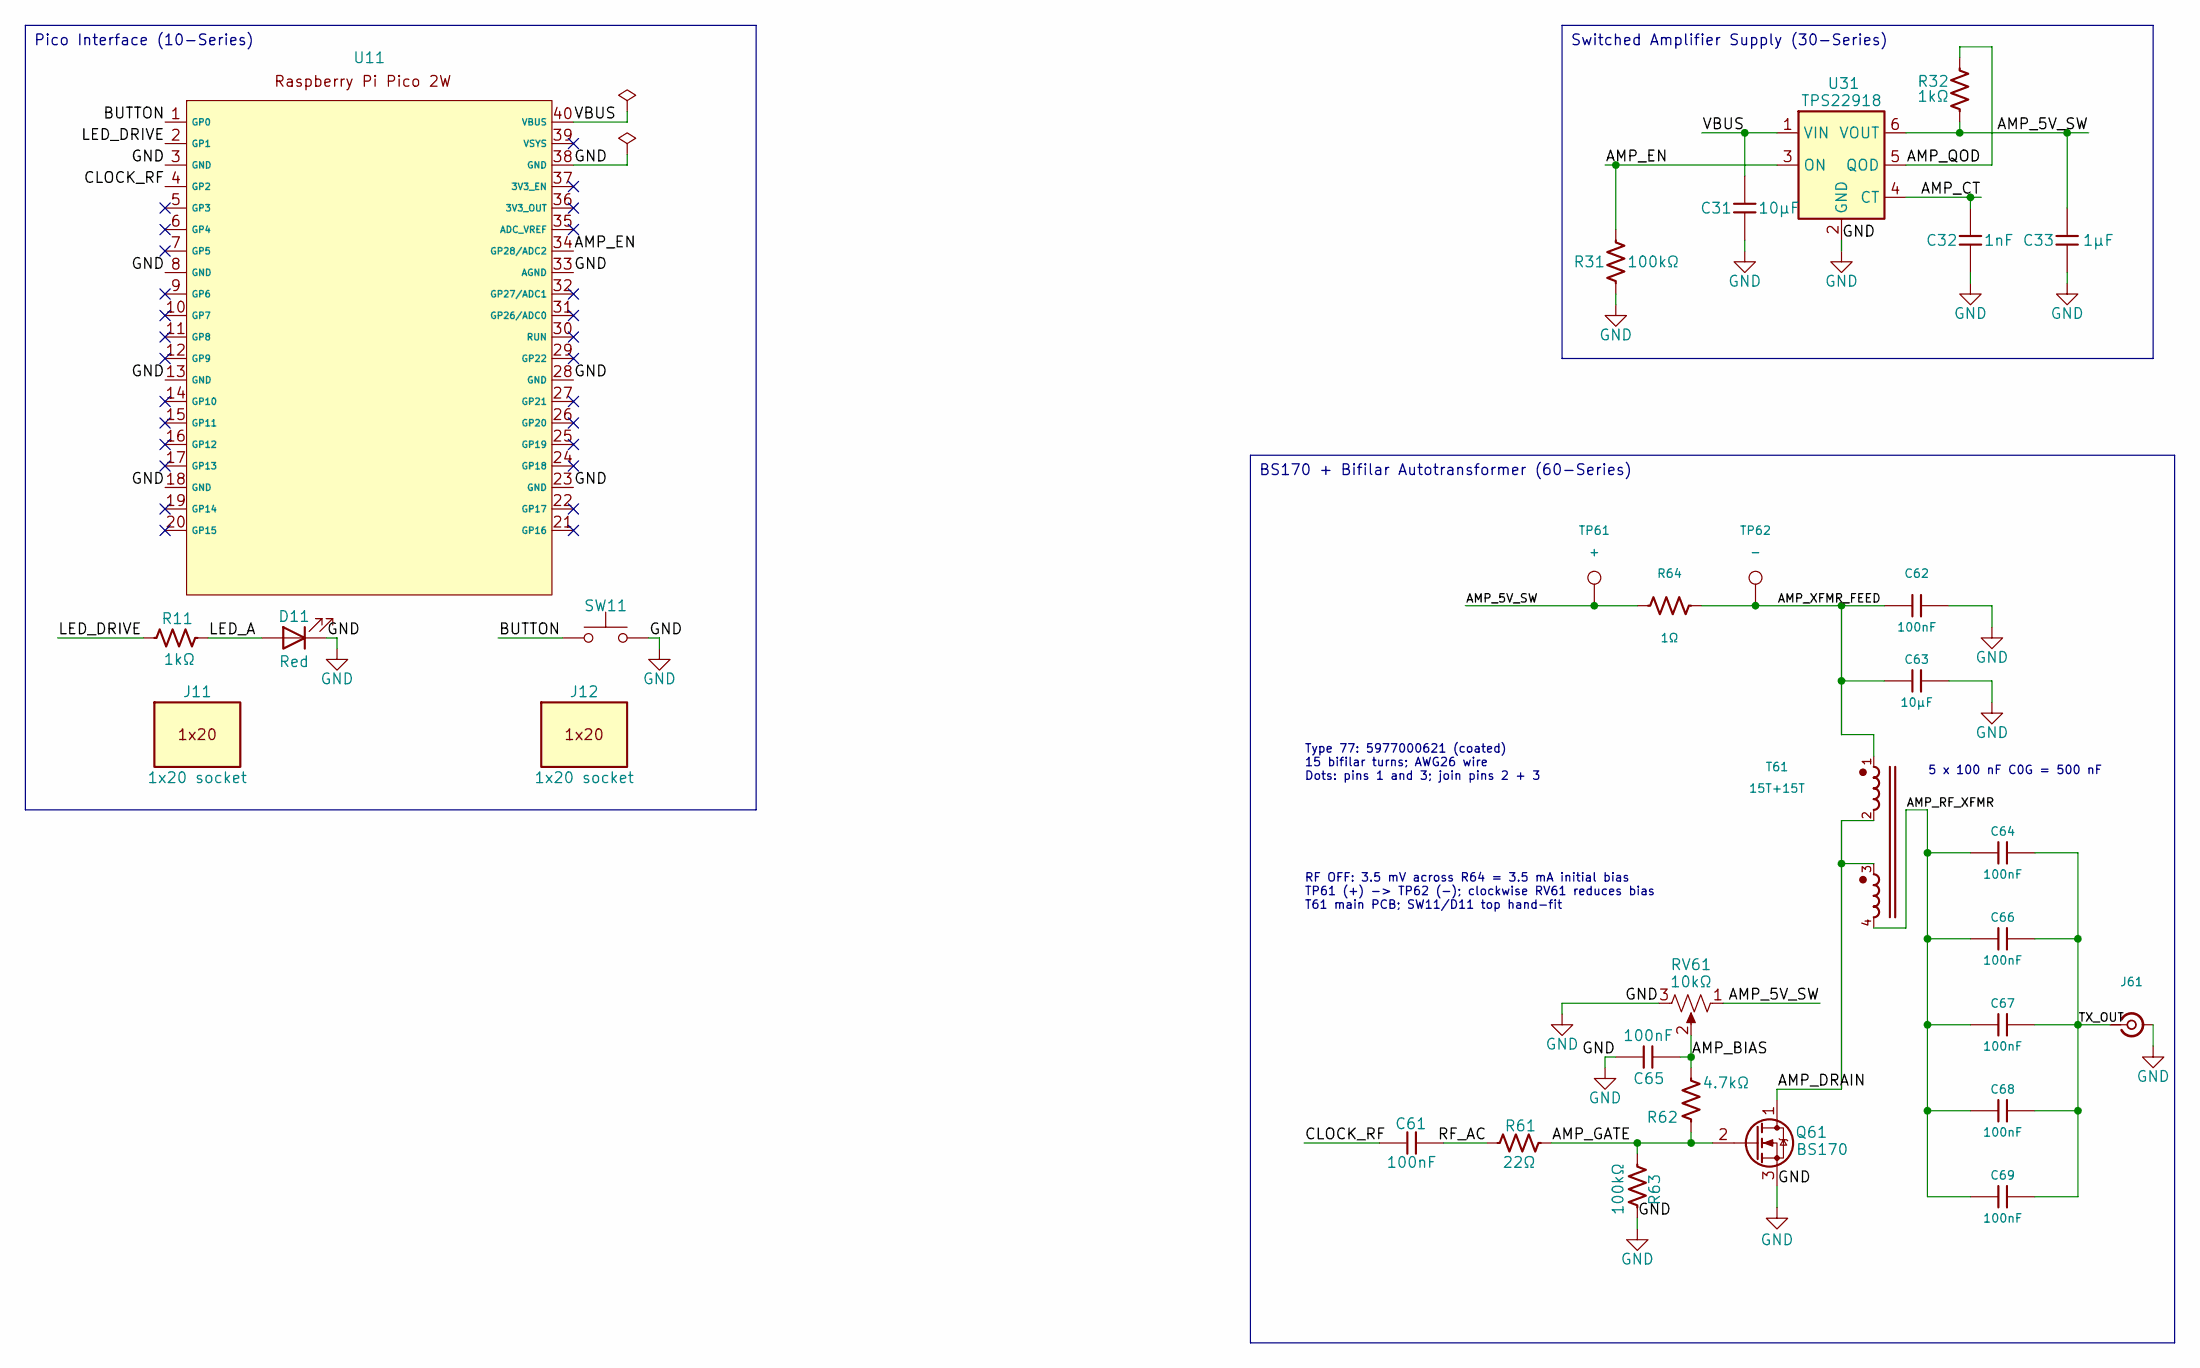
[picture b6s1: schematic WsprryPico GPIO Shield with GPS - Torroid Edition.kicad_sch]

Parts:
C31, C63: 10μF; C_1206_3216Metric; Tolerance 10%; Rating 25 V; MPN CL31B106KAHNNNE; LCSC Part # C14860
C32: 1nF; C_0603_1608Metric; Tolerance 5%; Rating 50 V; MPN CC0603JRNPO9BN102; LCSC Part # C106246
C33: 1μF; C_0805_2012Metric; Tolerance 10%; Rating 50 V; MPN AC0805KKX7R9BB105; LCSC Part # C726584
C61, C64, C66, C67, C68, C69: 100nF; C_1206_3216Metric; Tolerance 5%; Rating 50 V; MPN 1206N104J500CT; LCSC Part # C170182
C62, C65: 100nF; C_0603_1608Metric; Tolerance 10%; Rating 50 V; MPN FN18X104K500PBG; LCSC Part # C235731
D11: Red; LED_Kingbright_WP710A10LID_D3.0mm_P2.54mm_D1.3mm; Tolerance Datasheet; Rating 30 mA absolute max; about 1.2-1.6 mA wi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; MPN WP710A10LID; LCSC Part # C5879080
J11, J12: 1x20 socket; Tolerance Drawing dimensions; Rating 2.5 A nominal; MPN PM2.54-1*20; LCSC Part # C5224030
J61: SMA 50ohm; SMA_Adafruit_1865_EdgeMount; Tolerance Drawing dimensions; Rating 50 ohm; MPN 1865
Q61: BS170; TO-92_Inline; Tolerance Datasheet; Rating 60 V / 500 mA device limits; MPN BS170; LCSC Part # C111691
R11, R32: 1kΩ; R_0603_1608Metric; Tolerance 1%; Rating 100 mW; 75 V; MPN RC0603FR-071KL; LCSC Part # C22548
R31, R63: 100kΩ; R_0603_1608Metric; Tolerance 1%; Rating 100 mW; 75 V; MPN 0603WAF1003T5E; LCSC Part # C25803
R61: 22Ω; R_0603_1608Metric; Tolerance 1%; Rating 100 mW; 75 V; MPN 0603WAF220JT5E; LCSC Part # C23345
R62: 4.7kΩ; R_0603_1608Metric; Tolerance 1%; Rating 100 mW; 75 V; MPN RC0603FR-074K7L; LCSC Part # C99782
R64: 1Ω; R_1206_3216Metric; Tolerance 1%; Rating 250 mW; 200 V; +/-200 ppm/degC; MPN RC1206FR-071RL; LCSC Part # C137355
RV61: 10kΩ; Potentiometer_Bourns_TC33X_Vertical; Tolerance 25%; Rating 150 mW; MPN TC33X-2-103E; LCSC Part # C719176
SW11: Push; SW_PUSH_Alps_SKHLACA010; Tolerance Drawing dimensions; Rating 12 VDC / 50 mA contact limit; minimum 1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; MPN SKHLACA010; LCSC Part # C382056
T61: 15T+15T; T61_FairRite_5977000621_Upright_Bumper_4Pin; Tolerance Core AL +25%/-30%; winding and DC-bias 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; Rating Prototype 135.7 kHz-29.7 MHz target; RF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; MPN 5977000621
TP61: +; TestPoint_Pad_D1.0mm
TP62: -; TestPoint_Pad_D1.0mm
U11: Raspberry_Pi_Pico_2W_Header
U31: TPS22918; SOT-23-6; Tolerance Datasheet; Rating 5.5 V / 2 A device limits; MPN TPS22918DBVR; LCSC Part # C131941

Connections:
/AMP_5V_SW: C33.1, R32.2, R64.1, RV61.1, TP61.1 (1_1), U31.6 (VOUT)
/AMP_BIAS: C65.1, R62.1, RV61.2
/AMP_CT: C32.1, U31.4 (CT)
/AMP_DRAIN: Q61.1 (D), T61.2 (A_FINISH), T61.3 (B_START_DOT)
/AMP_EN: R31.1, U11.34 (GP28/ADC2), U31.3 (ON)
/AMP_GATE: Q61.2 (G), R61.2, R62.2, R63.1
/AMP_QOD: R32.1, U31.5 (QOD)
/AMP_RF_XFMR: C64.1, C66.1, C67.1, C68.1, C69.1, T61.4 (B_FINISH)
/AMP_XFMR_FEED: C62.1, C63.1, R64.2, T61.1 (A_START_DOT), TP62.1 (1_1)
/BUTTON: SW11.1, U11.1 (GP0)
/CLOCK_RF: C61.1, U11.4 (GP2)
/LED_A: D11.2 (A), R11.2
/LED_DRIVE: R11.1, U11.2 (GP1)
/RF_AC: C61.2, R61.1
/TX_OUT: C64.2, C66.2, C67.2, C68.2, C69.2, J61.1 (In)
/VBUS: C31.1, U11.40 (VBUS), U31.1 (VIN)
GND: C31.2, C32.2, C33.2, C62.2, C63.2, C65.2, D11.1 (K), J61.2 (GND), Q61.3 (S), R31.2, R63.2, RV61.3, SW11.2, U11.3 (GND), U11.8 (GND), U11.13 (GND), U11.18 (GND), U11.23 (GND), U11.28 (GND), U11.33 (AGND), U11.38 (GND), U31.2 (GND)

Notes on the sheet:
5 x 100 nF C0G = 500 nF
Type 77: 5977000621 (coated) 15 bifilar turns; AWG26 wire Dots: pins 1 and 3; join pins 2 + 3
RF OFF: 3.5 mV across R64 = 3.5 mA initial bias TP61 (+) -> TP62 (-); clockwise RV61 reduces bias T61 main PCB; SW11/D11 top hand-fit
Switched Amplifier Supply (30-Series)
Pico Interface (10-Series)
BS170 + Bifilar Autotransformer (60-Series)

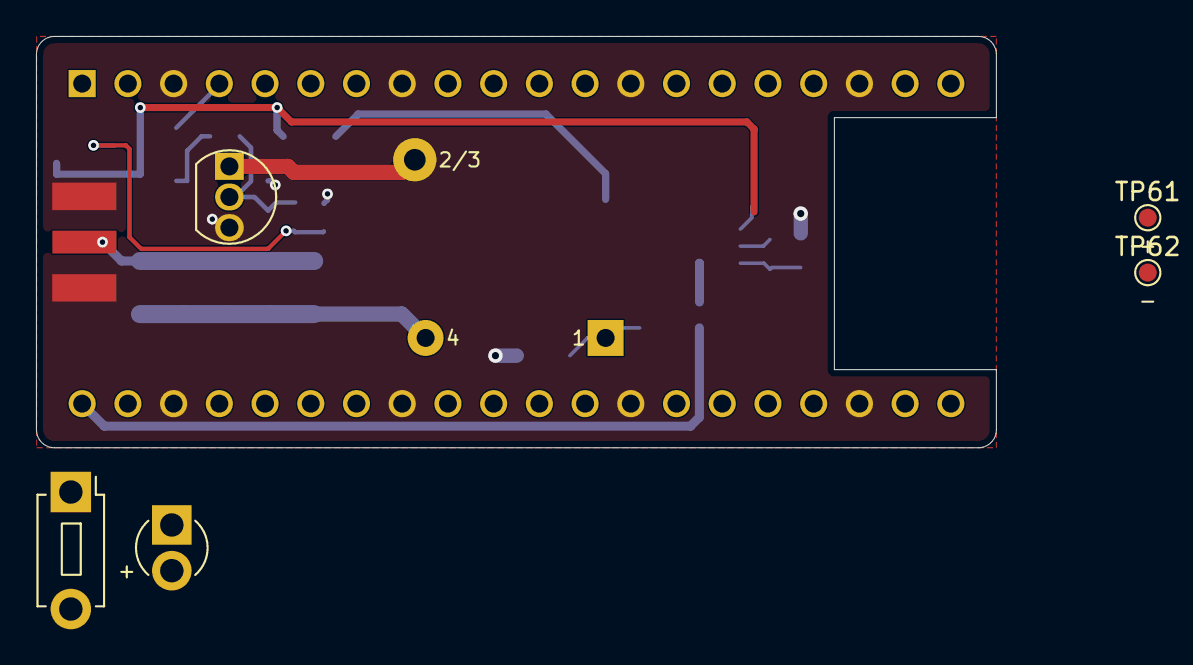
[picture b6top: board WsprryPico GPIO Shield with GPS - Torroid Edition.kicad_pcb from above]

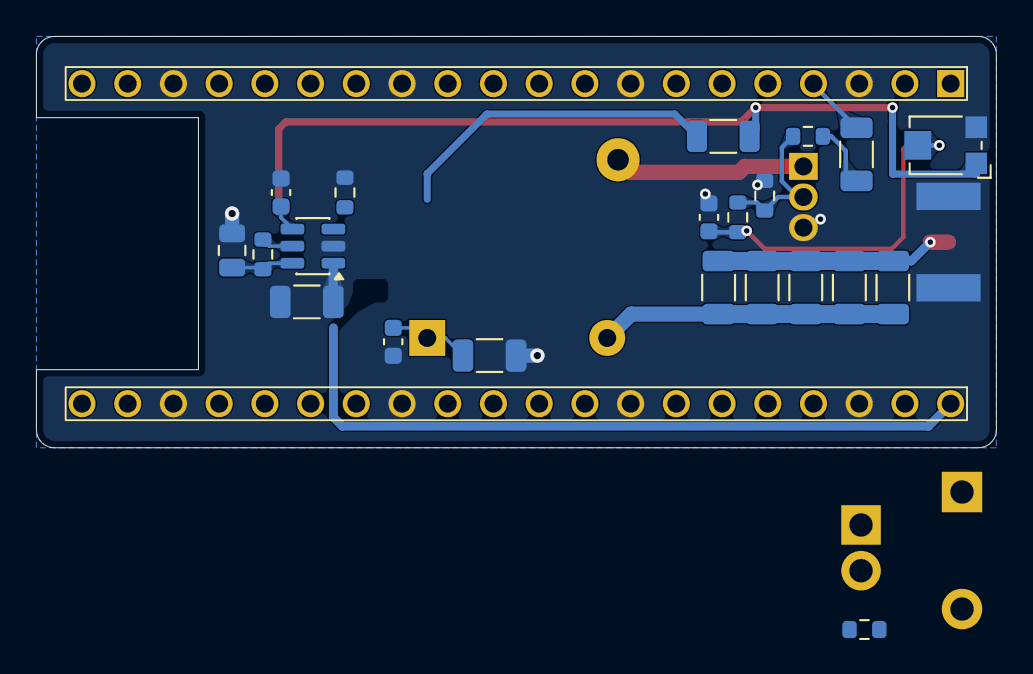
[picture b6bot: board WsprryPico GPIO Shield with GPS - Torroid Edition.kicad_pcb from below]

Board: 2 copper layers, 53.3 x 22.9 mm, 29 parts (22 on the bottom side), 17 nets.
